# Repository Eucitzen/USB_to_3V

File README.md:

# USB_to_3V
A simple PCB design for JLCPCB surface mount production that convers 5V to 3.3V

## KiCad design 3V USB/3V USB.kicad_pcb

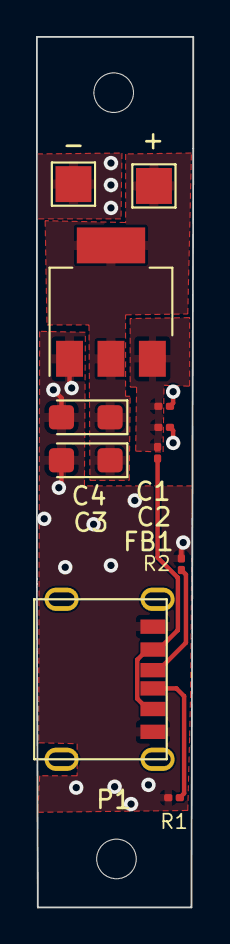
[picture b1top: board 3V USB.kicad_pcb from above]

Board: 2 copper layers, 8.7 x 48.4 mm, 13 parts (0 on the bottom side), 6 nets.

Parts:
C1: 10uF 0603; C_0201_0603Metric
C2: 1uF; C_0201_0603Metric
C3: 22uF tantalum; CP_EIA-3216-18_Kemet-A
C4: 1uF tantalum; CP_EIA-3216-18_Kemet-A
FB1: FerriteBead; L_0201_0603Metric
H1, H2: MountingHole; MountingHole_2.2mm_M2
P1: USB_C_Plug_USB2.0; TYPE-C-31-M-17
R1: 56k 0603; R_0201_0603Metric
R2: 56K 0603; R_0201_0603Metric
TP1, TP2: TestPoint; TestPoint_Pad_2.0x2.0mm
U1: AMS1117-3.3; SOT-223-3_TabPin2

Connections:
+3V3: C3.1, C4.1, TP1.1, U1.2 (VO)
+5V: C1.1, C2.1, FB1.2, U1.3 (VI)
/CC1: P1.A5 (CC), R2.1
/VBUS: FB1.1, P1.A4 (VBUS), P1.B9 (VBUS)
Earth: C1.2, C2.2, C3.2, C4.2, P1.A1 (GND), R1.2, R2.2, TP2.1, U1.1 (GND)
unnamed: P1.B5 (VCONN), R1.1

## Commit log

2024-11-12 PCB files and Kicad models added
    Added all that should be required to upload the files to JLCPCB and use their surface mount option. Should they be out of stock similar components of the same footprint may be used.
